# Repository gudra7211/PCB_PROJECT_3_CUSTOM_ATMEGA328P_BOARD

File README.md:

# PCB_PROJECT_3_CUSTOM_ATMEGA328P_BOARD

Hello there! Welcome to my third PCB design project, where I have created a custom ATMEGA328p board optimized for IoT applications that require extensive data logging. 
Unlike standard boards like the Arduino Uno, this board is designed to handle large datasets, making it ideal for applications like monitoring systems that collect continuous data over time. 
Equipped with a Real-Time Clock (RTC) module, this board enables precise time-stamped data collection.

Project Overview:  Tool Used: KiCAD, If you wish to download files from this repo note that you have to change your kiCAD project preferences in order to avoid any ERC or DRC errors. Board Layers:   The board can be designed with either 2 layers or 4 layers. Although the board can be designed using 2-layer, I experimented with a 4-layer design due to the complexity and number of connections in this project. Memory and Interfaces: The board features 2MB of memory and supports both I2C and UART interfaces, with dedicated pins for each. It also includes 7 GPIO (digital) pins for additional functionality. Programming: The board can be programmed using the onboard ICSP pins. Power Supply: The board can be powered using an external power supply through the pins marked "Battery" (please refer to the ATMEGA328p datasheet for maximum input voltage specifications).

Features:  IoT Benefits: Designed specifically for IoT projects, this board allows for more data logging compared to standard boards like the Arduino Uno. It provides extensive functionalities ideal for IoT applications, except for ADC (Analog to Digital Conversion). Real-Time Clock (RTC): The onboard RTC module enables precise time-stamped data collection, which is crucial for continuous monitoring and data analysis.

Note: The board does not support any analog pins as the internal ADC of the ATMEGA328p is disabled.

**Repository Structure** Branches:  main: General overview. 2Layer: Files and details specific to the 2-layer design. 4Layer: Files and details specific to the 4-layer design.
Feel free to explore the files in each branch to see the different design styles.

Note: You are currently viewing the main branch of this repository.

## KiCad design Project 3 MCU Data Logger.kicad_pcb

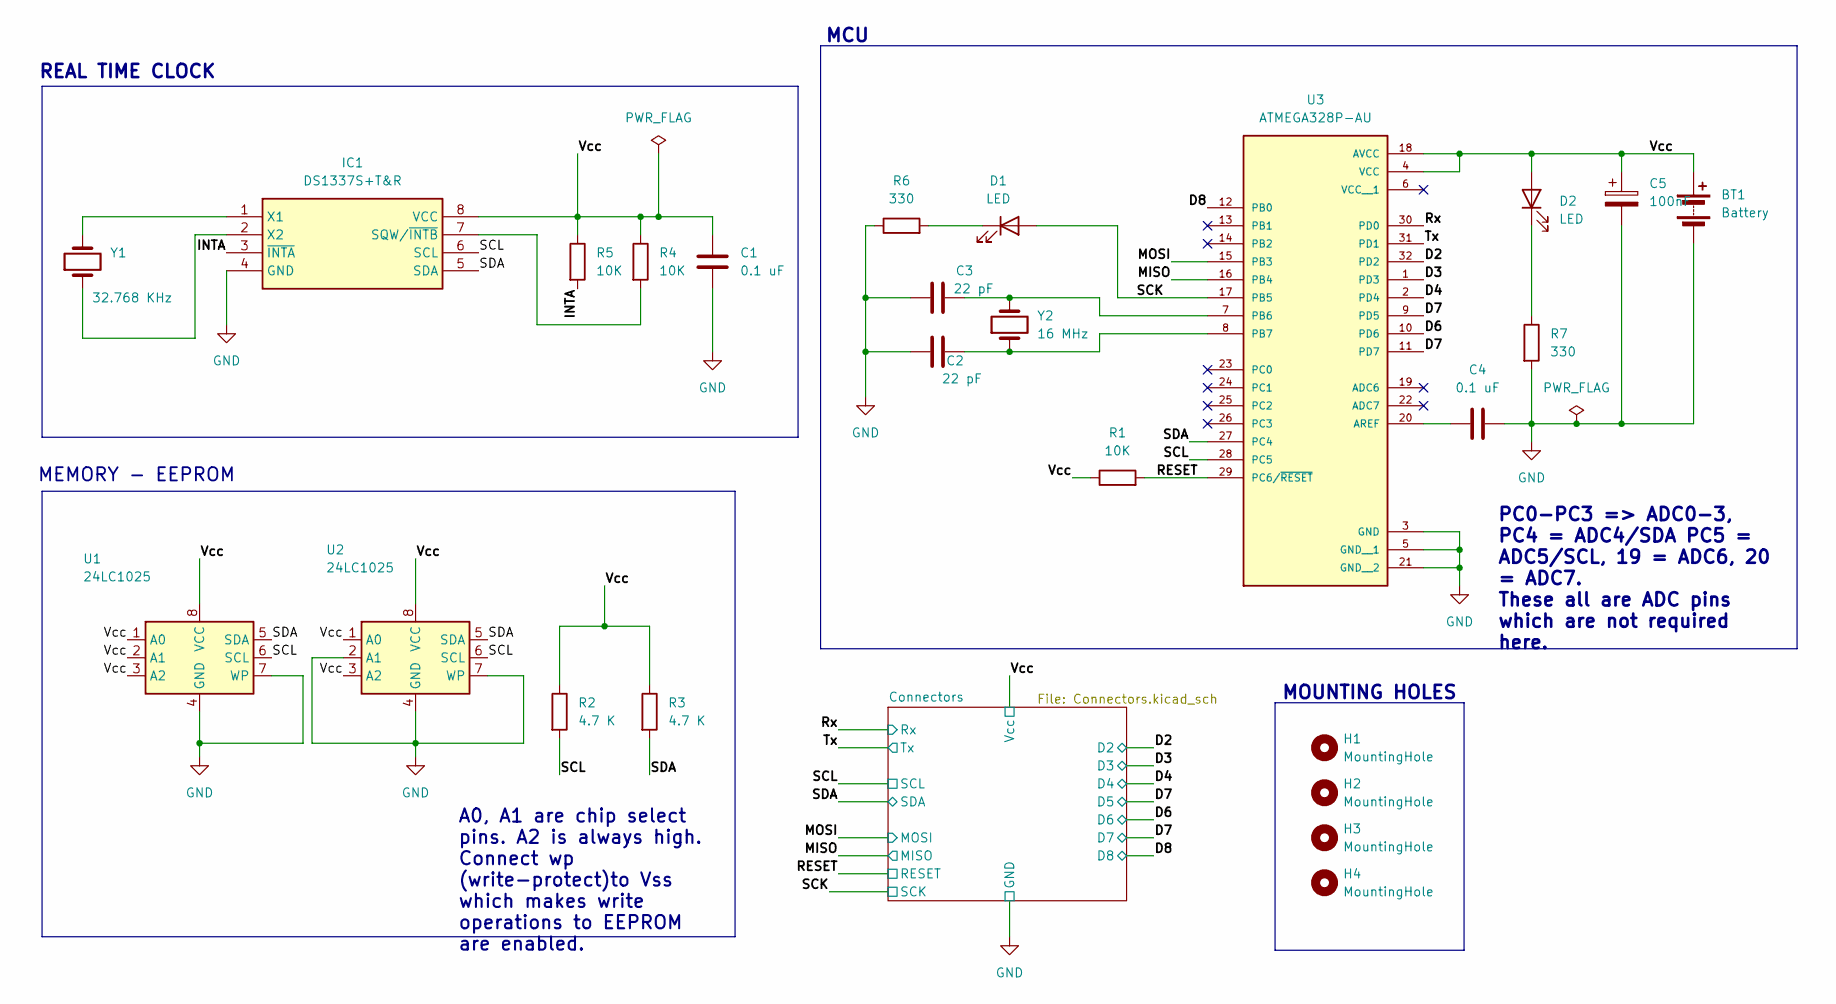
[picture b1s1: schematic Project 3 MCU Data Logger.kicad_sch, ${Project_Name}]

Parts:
BT1: Battery; PinHeader_1x02_P2.54mm_Vertical
C1, C4: 0.1 uF; C_0805_2012Metric
C2, C3: 22 pF; C_0805_2012Metric
C5: 100nF; C_0805_2012Metric
D1, D2: LED; LED_0805_2012Metric
H1, H2, H3, H4: MountingHole; MountingHole_2.1mm
IC1: DS1337S+T&R; SOIC127P600X175-8N; Manufacturer_Part_Number DS1337S+T&R; Mouser Part Number 700-DS1337ST&R
R1, R4, R5: 10K; R_0805_2012Metric
R2, R3: 4.7 K; R_0805_2012Metric
R6, R7: 330; R_0805_2012Metric
U1, U2: 24LC1025; SOIC-8_5.23x5.23mm_P1.27mm
U3: ATMEGA328P-AU; QFP80P900X900X120-32N; PARTREV 8271A
Y1: 32.768 KHz; Crystal_SMD_5032-2Pin_5.0x3.2mm_HandSoldering
Y2: 16 MHz; Crystal_SMD_5032-2Pin_5.0x3.2mm_HandSoldering

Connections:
/D2: U3.32 (PD2); also elsewhere on the board
/D3: U3.1 (PD3); also elsewhere on the board
/D4: U3.2 (PD4); also elsewhere on the board
/D6: U3.10 (PD6); also elsewhere on the board
/D7: U3.9 (PD5), U3.11 (PD7); also elsewhere on the board
/D8: U3.12 (PB0); also elsewhere on the board
/INTA: IC1.3 (~INTA), R5.2
/MISO: U3.16 (PB4); also elsewhere on the board
/MOSI: U3.15 (PB3); also elsewhere on the board
/RESET: R1.2, U3.29 (PC6/~RESET); also elsewhere on the board
/Rx: U3.30 (PD0); also elsewhere on the board
/SCK: D1.2 (A), U3.17 (PB5); also elsewhere on the board
/SCL: IC1.6 (SCL), R2.2, U1.6 (SCL), U2.6 (SCL), U3.28 (PC5); also elsewhere on the board
/SDA: IC1.5 (SDA), R3.2, U1.5 (SDA), U2.5 (SDA), U3.27 (PC4); also elsewhere on the board
/Tx: U3.31 (PD1); also elsewhere on the board
/Vcc: BT1.1 (+), C1.1, C5.1, D2.2 (A), IC1.8 (VCC), R1.1, R2.1, R3.1, R4.1, R5.1, U1.1 (A0), U1.2 (A1), U1.3 (A2), U1.8 (VCC), U2.1 (A0), U2.3 (A2), U2.8 (VCC), U3.4 (VCC), U3.18 (AVCC); also elsewhere on the board
GND: BT1.2 (-), C1.2, C2.1, C3.1, C4.2, C5.2, IC1.4 (GND), R6.1, R7.2, U1.4 (GND), U1.7 (WP), U2.2 (A1), U2.4 (GND), U2.7 (WP), U3.3 (GND), U3.5 (GND__1), U3.21 (GND__2); also elsewhere on the board
unnamed: D1.1 (K), R6.2
unnamed: D2.1 (K), R7.1
unnamed: IC1.7 (SQW/~INTB), R4.2
unnamed: IC1.1 (X1), Y1.2
unnamed: IC1.2 (X2), Y1.1
unnamed: C4.1, U3.20 (AREF)
unnamed: C3.2, U3.7 (PB6), Y2.2
unnamed: C2.2, U3.8 (PB7), Y2.1

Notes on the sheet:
PC0-PC3 => ADC0-3, PC4 = ADC4/SDA PC5 = ADC5/SCL, 19 = ADC6, 20 = ADC7. These all are ADC pins which are not required here.
A0, A1 are chip select pins. A2 is always high. Connect wp (write-protect)to Vss which makes write operations to EEPROM are enabled.
MOUNTING HOLES
MCU
MEMORY - EEPROM
REAL TIME CLOCK

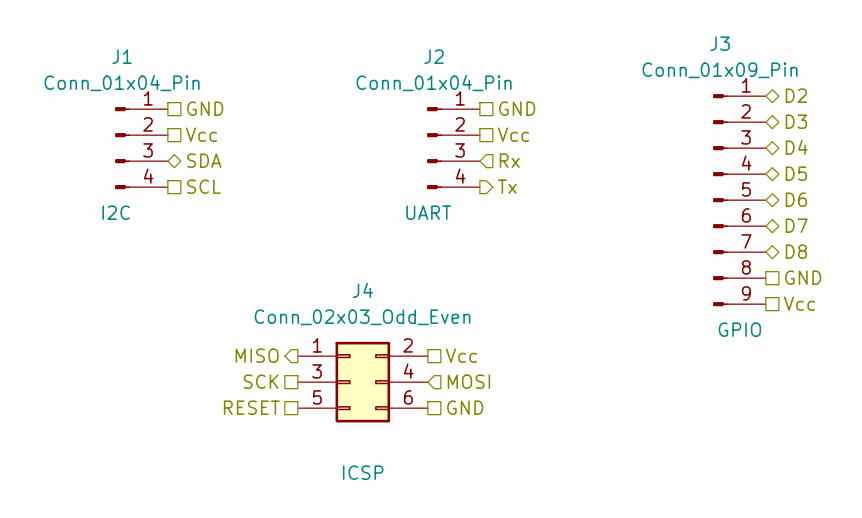
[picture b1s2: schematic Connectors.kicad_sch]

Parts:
J1, J2: Conn_01x04_Pin; PinHeader_1x04_P2.54mm_Vertical
J3: Conn_01x09_Pin; PinHeader_1x09_P2.54mm_Vertical
J4: Conn_02x03_Odd_Even; PinHeader_2x03_P2.54mm_Vertical

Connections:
/D2: J3.1; also elsewhere on the board
/D3: J3.2; also elsewhere on the board
/D4: J3.3; also elsewhere on the board
/D6: J3.5; also elsewhere on the board
/D7: J3.4, J3.6; also elsewhere on the board
/D8: J3.7; also elsewhere on the board
/MISO: J4.1; also elsewhere on the board
/MOSI: J4.4; also elsewhere on the board
/RESET: J4.5; also elsewhere on the board
/Rx: J2.3; also elsewhere on the board
/SCK: J4.3; also elsewhere on the board
/SCL: J1.4; also elsewhere on the board
/SDA: J1.3; also elsewhere on the board
/Tx: J2.4; also elsewhere on the board
/Vcc: J1.2, J2.2, J3.9, J4.2; also elsewhere on the board
GND: J1.1, J2.1, J3.8, J4.6; also elsewhere on the board

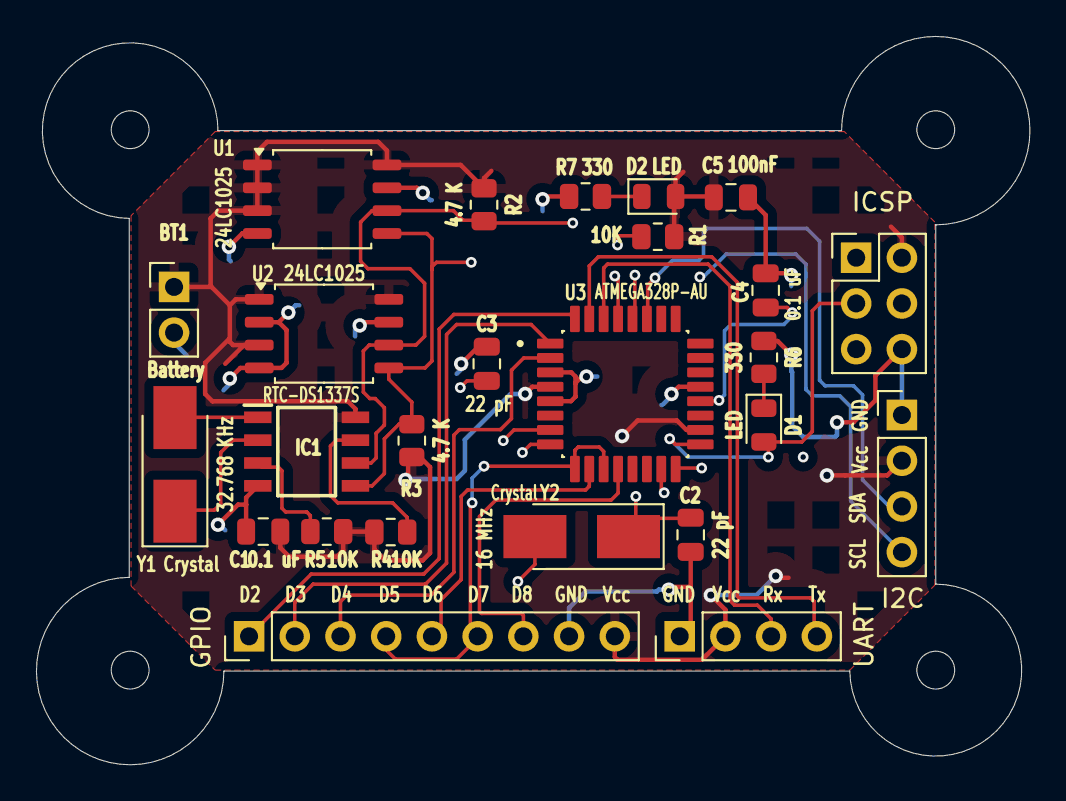
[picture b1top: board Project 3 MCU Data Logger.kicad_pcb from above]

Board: 4 copper layers, 55.2 x 40.5 mm, 29 parts (0 on the bottom side), 25 nets.

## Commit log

2024-08-04 Uploading Files to 2 layered branch
2024-08-04 Update README.md of 2Layered B
